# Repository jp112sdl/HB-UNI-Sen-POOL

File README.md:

# HB-UNI-Sen-POOL

### ⚠️ Achtung: RX und TX am FTDI Anschluss sind vertauscht!

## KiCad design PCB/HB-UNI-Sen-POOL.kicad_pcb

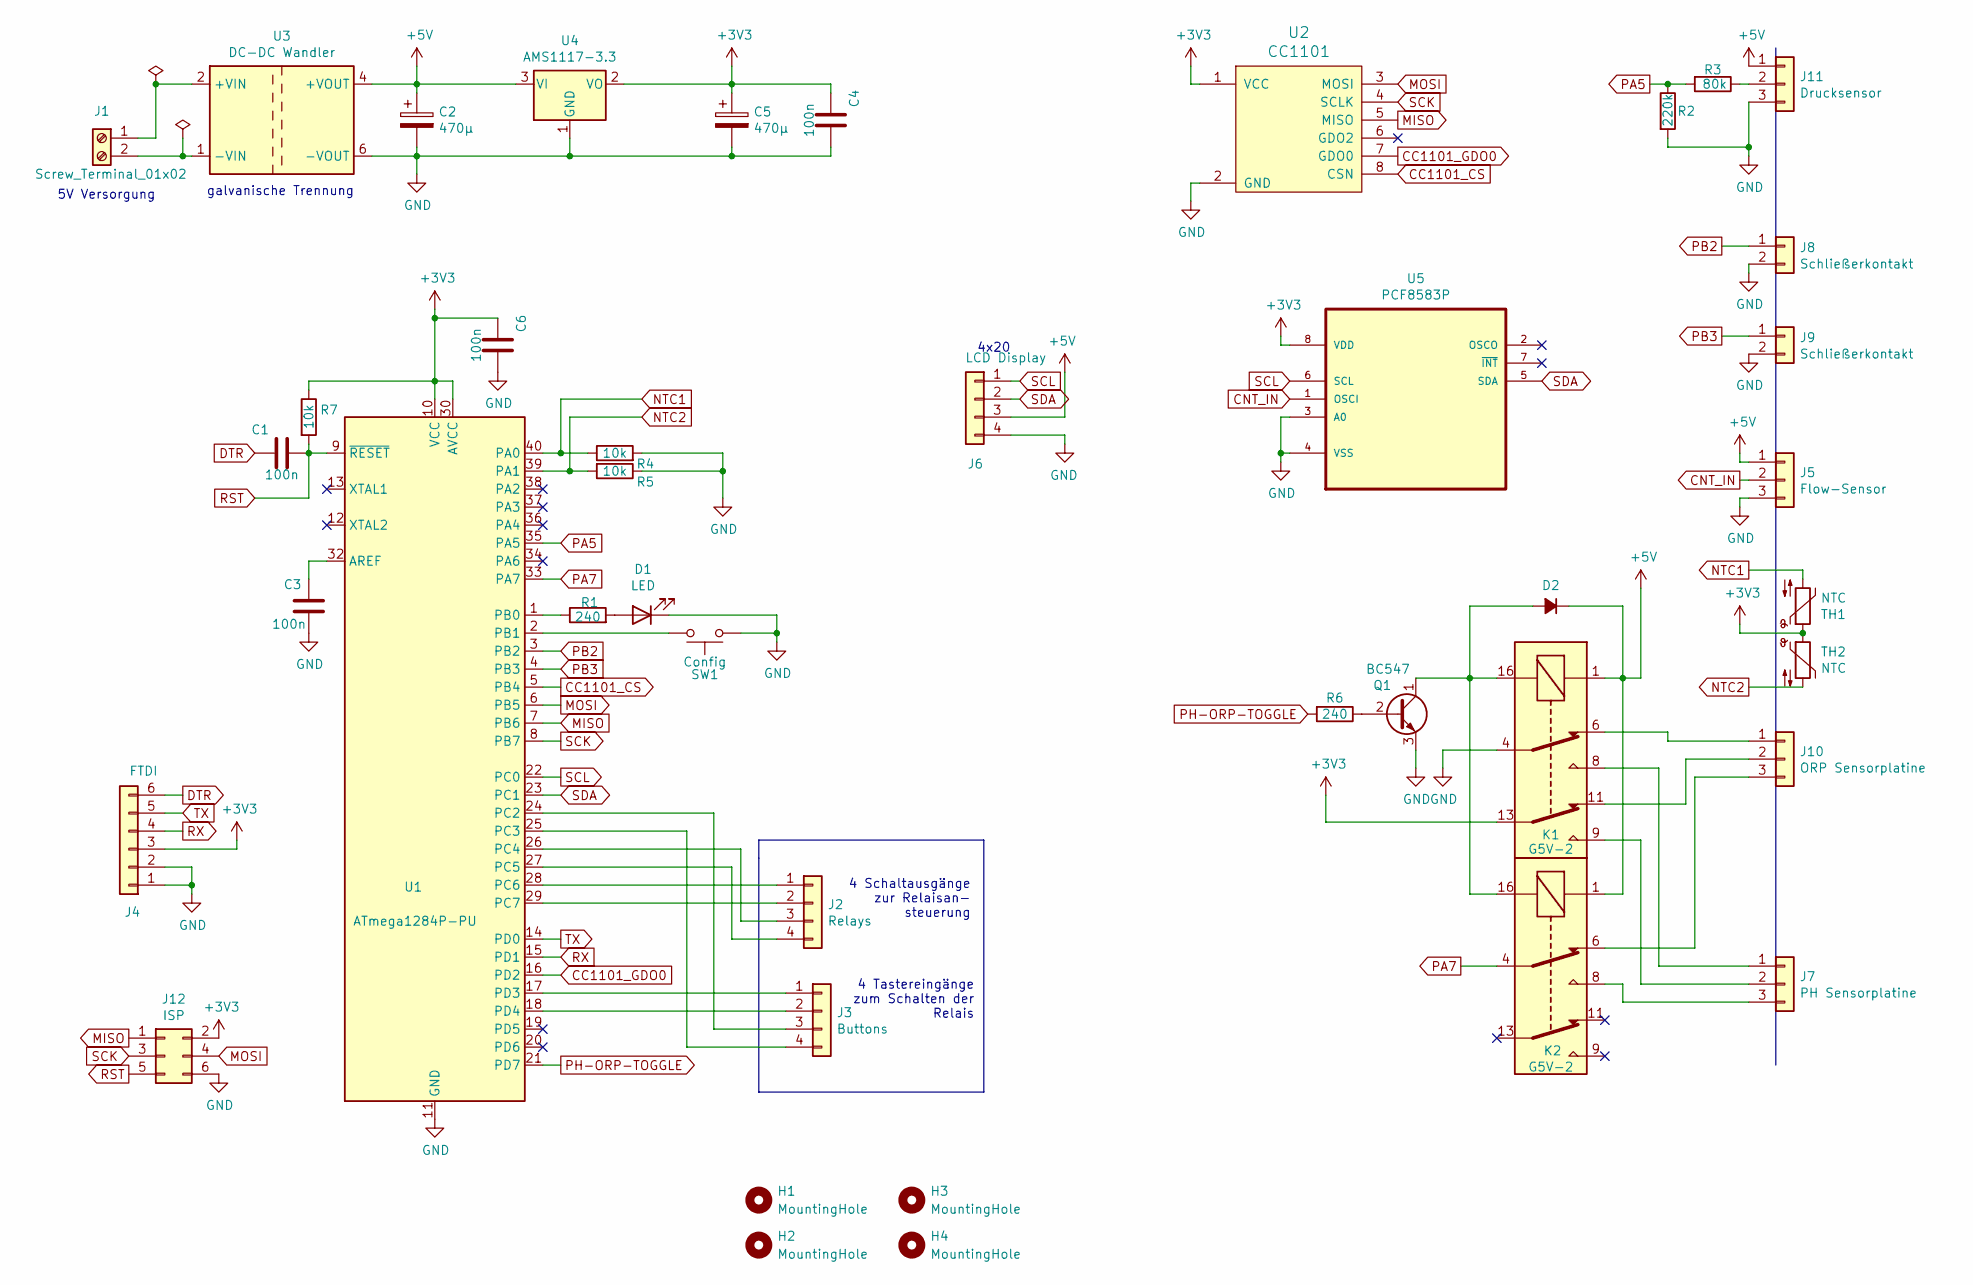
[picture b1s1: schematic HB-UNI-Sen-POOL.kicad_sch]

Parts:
C1, C3, C4, C6: 100n; C_Rect_L10.0mm_W2.5mm_P7.50mm_MKS4
C2, C5: 470µ; CP_Radial_D8.0mm_P3.50mm
D1: LED; LED_D5.0mm
D2: D_Small_ALT; D_DO-35_SOD27_P7.62mm_Horizontal
H1, H2, H3, H4: MountingHole; MountingHole_2.5mm_Pad
J1: Screw_Terminal_01x02; PhoenixContact_MSTBA_2,5_2-G-5,08_1x02_P5.08mm_Horizontal
J2: Relays; PinHeader_1x04_P2.54mm_Vertical
J3: Buttons; PinHeader_1x04_P2.54mm_Vertical
J4: FTDI; PinHeader_1x06_P2.54mm_Vertical
J5: Flow-Sensor; PinHeader_1x03_P2.54mm_Vertical
J6: LCD Display; PinHeader_1x04_P2.54mm_Vertical
J7: PH Sensorplatine; PinHeader_1x03_P2.54mm_Vertical
J8, J9: Schließerkontakt; PinHeader_1x02_P2.54mm_Vertical
J10: ORP Sensorplatine; PinHeader_1x03_P2.54mm_Vertical
J11: Drucksensor; PinHeader_1x03_P2.54mm_Vertical
J12: ISP; PinHeader_2x03_P2.54mm_Vertical
K1, K2: G5V-2; Relay_DPDT_Omron_G5V-2
Q1: BC547; TO-92_Inline
R1, R6: 240; R_Axial_DIN0207_L6.3mm_D2.5mm_P10.16mm_Horizontal
R2: 220k; R_Axial_DIN0207_L6.3mm_D2.5mm_P10.16mm_Horizontal
R3: 80k; R_Axial_DIN0207_L6.3mm_D2.5mm_P10.16mm_Horizontal
R4, R5, R7: 10k; R_Axial_DIN0207_L6.3mm_D2.5mm_P10.16mm_Horizontal
SW1: Config; SW_PUSH_6mm_H13mm
TH1, TH2: NTC; PinHeader_1x02_P2.54mm_Vertical
U1: ATmega1284P-PU; DIP-40_W15.24mm
U2: CC1101; PinSocket_1x08_P2.00mm_Vertical
U3: DC-DC Wandler; Converter_DCDC_TRACO_TMR-1-xxxx_Single_THT
U4: AMS1117-3.3; SOT-223-3_TabPin2
U5: PCF8583P; DIP254P762X420-8; MPN PCF8583P

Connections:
+3V3: C4.2, C5.1, C6.2, J4.3, J12.2, K1.13, R7.1, TH1.1, TH2.1, U1.10 (VCC), U1.30 (AVCC), U2.1 (VCC), U4.2 (VO), U5.8 (VDD)
+5V: C2.1, D2.1 (K), J5.1, J6.3, J11.1, K1.1, K2.1, U3.4 (+VOUT), U4.3 (VI)
CC1101_CS: U1.5 (PB4), U2.8 (CSN)
CC1101_GDO0: U1.16 (PD2), U2.7 (GDO0)
CNT_IN: J5.2, U5.1 (OSCI)
DTR: C1.2, J4.6
GND: C2.2, C3.1, C4.1, C5.2, C6.1, D1.1 (K), J4.1, J4.2, J5.3, J6.4, J8.2, J9.2, J11.3, J12.6, K1.4, Q1.3 (E), R2.2, R4.2, R5.1, SW1.1, U1.11 (GND), U1.31 (GND), U2.2 (GND), U3.6 (-VOUT), U4.1 (GND), U5.3 (A0), U5.4 (VSS)
MISO: J12.1, U1.7 (PB6), U2.5 (MISO)
MOSI: J12.4, U1.6 (PB5), U2.3 (MOSI)
NTC1: R4.1, TH1.2, U1.40 (PA0)
NTC2: R5.2, TH2.2, U1.39 (PA1)
unnamed: C3.2, U1.32 (AREF)
unnamed: D1.2 (A), R1.2
unnamed: D2.2 (A), K1.16, K2.16, Q1.1 (C)
unnamed: J1.1, U3.2 (+VIN)
unnamed: J1.2, U3.1 (-VIN)
unnamed: J2.1, U1.28 (PC6)
unnamed: J2.2, U1.29 (PC7)
unnamed: J2.3, U1.26 (PC4)
unnamed: J2.4, U1.27 (PC5)
unnamed: J3.1, U1.17 (PD3)
unnamed: J3.2, U1.18 (PD4)
unnamed: J3.3, U1.24 (PC2)
unnamed: J3.4, U1.25 (PC3)
unnamed: J7.1, K1.8
unnamed: J7.2, K1.9
unnamed: J7.3, K2.8
unnamed: J10.1, K1.6
unnamed: J10.2, K1.11
unnamed: J10.3, K2.6
unnamed: J11.2, R3.1
unnamed: Q1.2 (B), R6.1
unnamed: R1.1, U1.1 (PB0)
unnamed: SW1.2, U1.2 (PB1)
PA5: R2.1, R3.2, U1.35 (PA5)
PA7: K2.4, U1.33 (PA7)
PB2: J8.1, U1.3 (PB2)
PB3: J9.1, U1.4 (PB3)
PH-ORP-TOGGLE: R6.2, U1.21 (PD7)
RST: C1.1, J12.5, R7.2, U1.9 (~RESET)
RX: J4.4, U1.15 (PD1)
SCK: J12.3, U1.8 (PB7), U2.4 (SCLK)
SCL: J6.1, U1.22 (PC0), U5.6 (SCL)
SDA: J6.2, U1.23 (PC1), U5.5 (SDA)
TX: J4.5, U1.14 (PD0)

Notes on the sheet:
4 Tastereingänge zum Schalten der Relais
5V Versorgung
galvanische Trennung
4x20
4 Schaltausgänge zur Relaisan- steuerung

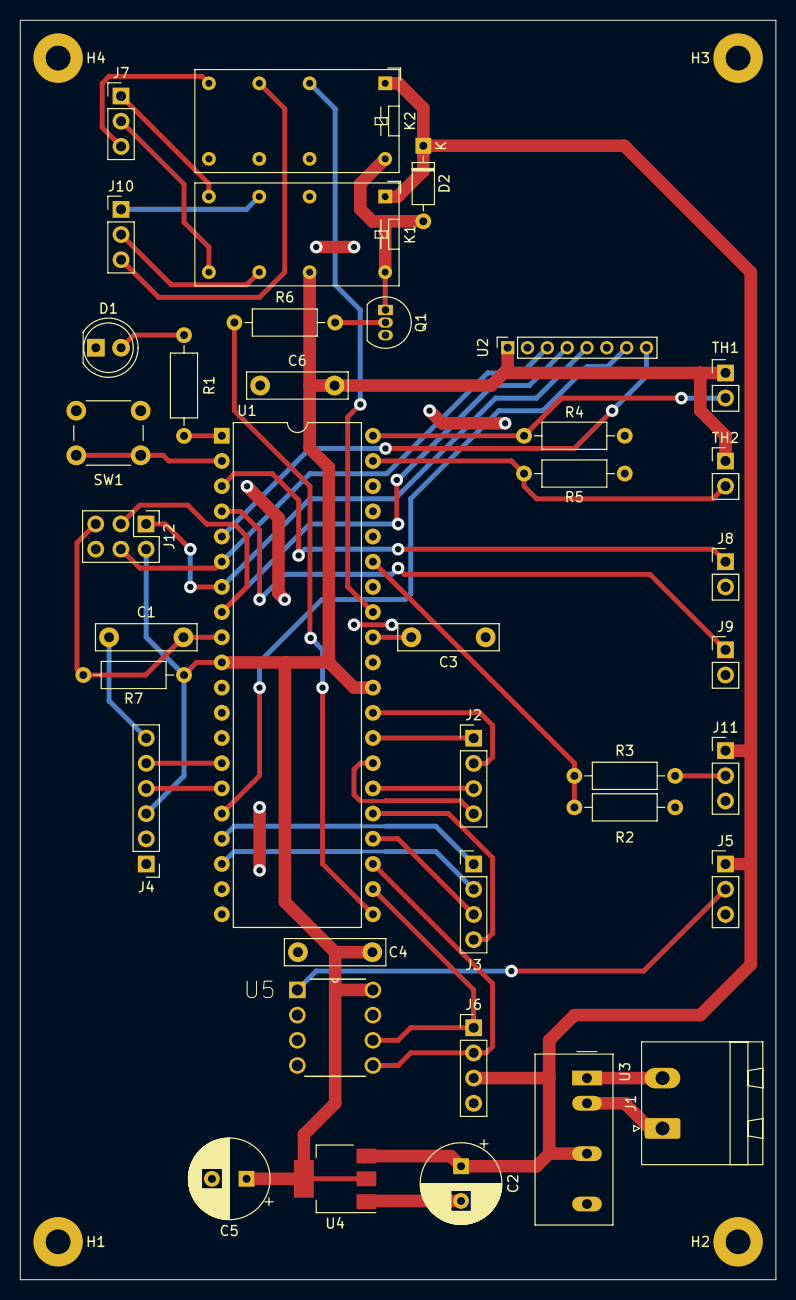
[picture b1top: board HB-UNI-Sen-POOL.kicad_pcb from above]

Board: 2 copper layers, 76.2 x 127.0 mm, 42 parts (0 on the bottom side), 45 nets.

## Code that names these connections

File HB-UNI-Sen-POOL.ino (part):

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#define LCD_ROWS           4
#define LCD_COLUMNS        20

#define NTC_SENSE_PIN_1      A0 //PA0
#define NTC_SENSE_PIN_2      A1 //PA1
                                //PA2
                                //PA3
                                //PA4
#define PRESSURE_PIN         A5 //PA5
                                //PA6
#define ORPH_SIGNAL_PIN      A7 //PA7

#define LED_PIN              0  //PB0
#define CONFIG_BUTTON_PIN    1  //PB1
#define SC_1_PIN             2  //PB2
#define SC_2_PIN             3  //PB3
#define CC1101_CS_PIN        4  //PB4
                                //PB5...7 SPI

                                //PC0...1 I2C
#define SW_BUTTON_PIN_3      18 //PC2
#define SW_BUTTON_PIN_4      19 //PC3
#define RELAY_PIN_3          20 //PC4
#define RELAY_PIN_4          21 //PC5
#define RELAY_PIN_1          22 //PC6
#define RELAY_PIN_2          23 //PC7

                                //PD0...1 TX/RX FTDI
#define CC1101_GDO0          10 //PD2
#define SW_BUTTON_PIN_1      11 //PD3
#define SW_BUTTON_PIN_2      12 //PD4
                                //PD5
                                //PD6
#define SENSOR_SWITCH_PIN    15 //PD7
#define OFF LOW
#define ON  HIGH

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  {0x01, 0x01}                 // Info Bytes
};

typedef AskSin<StatusLed<LED_PIN>, NoBattery, Radio<LibSPI<CC1101_CS_PIN>, CC1101_GDO0>> Hal;
Hal hal;

DEFREGISTER(UReg0, MASTERID_REGS, 0x1f, 0x20, 0x21, DREG_BACKONTIME, DREG_INTKEY)
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private:
    MeasureEventMsg   msg;
    UserStorage       us;
    Ntc<NTC_SENSE_PIN_1,NTC_R0,NTC_B,0 ,NTC_T0,NTC_OVERSAMPLING> ntc1;
    Ntc<NTC_SENSE_PIN_2,NTC_R0,NTC_B,0 ,NTC_T0,NTC_OVERSAMPLING> ntc2;
    PCF8583           pcf8583;
    bool              phcalibrationMode;
    bool              first;
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
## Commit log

2021-05-01 add images
2021-05-01 show error in ccu when calibration data are invalid
2021-05-03 first (dry run) pcf8583 implementation
2021-05-03 add relay pin to switch between PH and ORP sensor
2021-05-07 add schematics
2021-05-14 flow measurement
2021-05-17 disable voltage display timer
2021-06-11 add doc
2021-11-22 Create a simple two layer PCB for this schematic
    Update the schematic with a few minor changes
    revised some footprints
    added one more bypass capacitor C6
    added mounting holes
    Create simple two layer PCB
    ground pour on bottom layer
2021-11-29 update image/pdf
2022-06-26 use measured - not dummy - values

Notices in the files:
HB-UNI-Sen-POOL.ino:
2016-10-31 papa Creative Commons - http://creativecommons.org/licenses/by-nc-sa/3.0/de
2021-03-03 jp112sdl Creative Commons - http://creativecommons.org/licenses/by-nc-sa/3.0/de
